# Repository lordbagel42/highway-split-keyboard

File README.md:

# Turing Split - HIGHWAY

<sub>this ^ will be replaced with a photo of the actual keyboard once it's built</sub>

## why?

I type a lot. Like, an insane amount. I write code for my robotics team and a lot for Hack Club, so I need a decent keyboard.
I've been using the Apple Magic Keyboard for a long while, and it's honestly quite nice. I originally bought it because my Quest 2 can track it.

However, I also am prone to carpal tunnel and other hand/fingie-issues, so I figured I should get a keyboard.
This led me to a discovery: Keyboards, are not cheap.

Then I discovered Highway and had a thought: make someone else pay for my keyboard.

## my keyboard design

I was tempted to go all out and build a full desk size keyboard contraption, but then I found [ergogen](https://ergogen.ceoloide.com/?exp=kicanvas) and decided to make an ergonomic, split-deck keyboard.
I based this off of a lot of random keyboards I saw throughout the internet and had one main focus when designing: comfortable, but not confusing.

I like layers. I plan to use them. I also want to have enough buttons I can do things easily and without thinking. If I wanted chords, I would have made a stenography keyboard.

This isn't the most complicated design, it's not the most simple, but it is mine, and I feel happy with it.

## the bom

Overall, the cost comes out to about $180 w/ tax.

| ITEM                  | SUPPLIER        | COUNT | UNIT COST | ROW COST | LOW BUDGET USE | HIGH BUDGET USE |
| --------------------- | --------------- | ----- | --------- | -------- | -------------- | --------------- |
| nice!nano v2          | typeractive.xyz | 1     | $25.00    | $25.00   | 17%            | 7%              |
| nice!view             | typeractive.xyz | 1     | $20.00    | $20.00   | 13%            | 6%              |
| PCB                   | JLCPCB          | 1     | $12.00    | $12.00   | 8%             | 3%              |
| PCB Shipping          | JLCPCB          | 1     | $25.00    | $25.00   | 17%            | 7%              |
| Kailh Hotswap Sockets | typeractive.xyz | 60    | $0.15     | $9.00    | 6%             | 3%              |
| Battery Jack          | typeractive.xyz | 2     | $0.50     | $1.00    | 1%             | 0%              |
| 1.5u Keycap           | typeractive.xyz | 4     | $0.50     | $2.00    | 1%             | 1%              |
| Homing Keycap         | typeractive.xyz | 2     | $0.50     | $1.00    | 1%             | 0%              |
| Keycap                | typeractive.xyz | 50    | $0.40     | $20.00   | 13%            | 6%              |
| Choc Switches         | typeractive.xyz | 60    | $0.55     | $33.00   | 22%            | 9%              |
| Diodes                | typeractive.xyz | 60    | $0.08     | $4.50    | 3%             | 1%              |
| Power Switch          | typeractive.xyz | 2     | $0.75     | $1.50    | 1%             | 0%              |
| Sockets and Pins      | typeractive.xyz | 2     | $6.50     | $13.00   | 9%             | 4%              |
| Encoder               | aliexpress      | 2     | $1.10     | $2.20    | 1%             | 1%              |

## notes

Something to note about this is a bit of a habit I've picked up from my apple keyboard: I don't like thick keyboards. My magic keyboard is maybe 7 millimeters tall at maximum and about 3 at the minimum. I am okay with something a bit thicker, but I don't want something as thick as a normal keyboard.

This is also part of why I went for low profile keys and keycaps, hence the Choc switches instead of the more common MX switches.

I also don't want a case to help with that. Because of the requirements for Highway, I have one. It's a very thin case designed to be lasercut using acrylic and 3d printed standoffs.

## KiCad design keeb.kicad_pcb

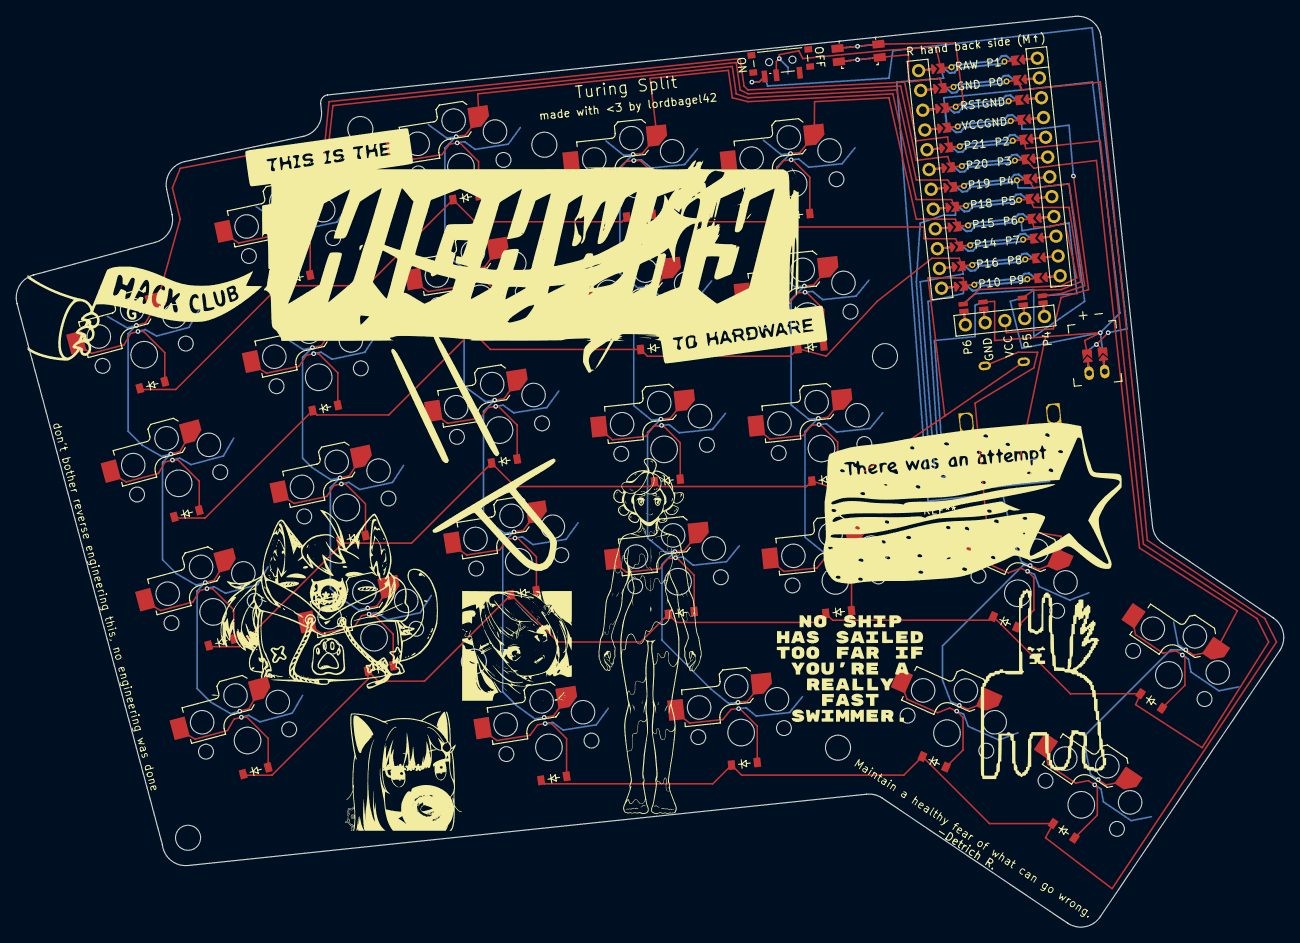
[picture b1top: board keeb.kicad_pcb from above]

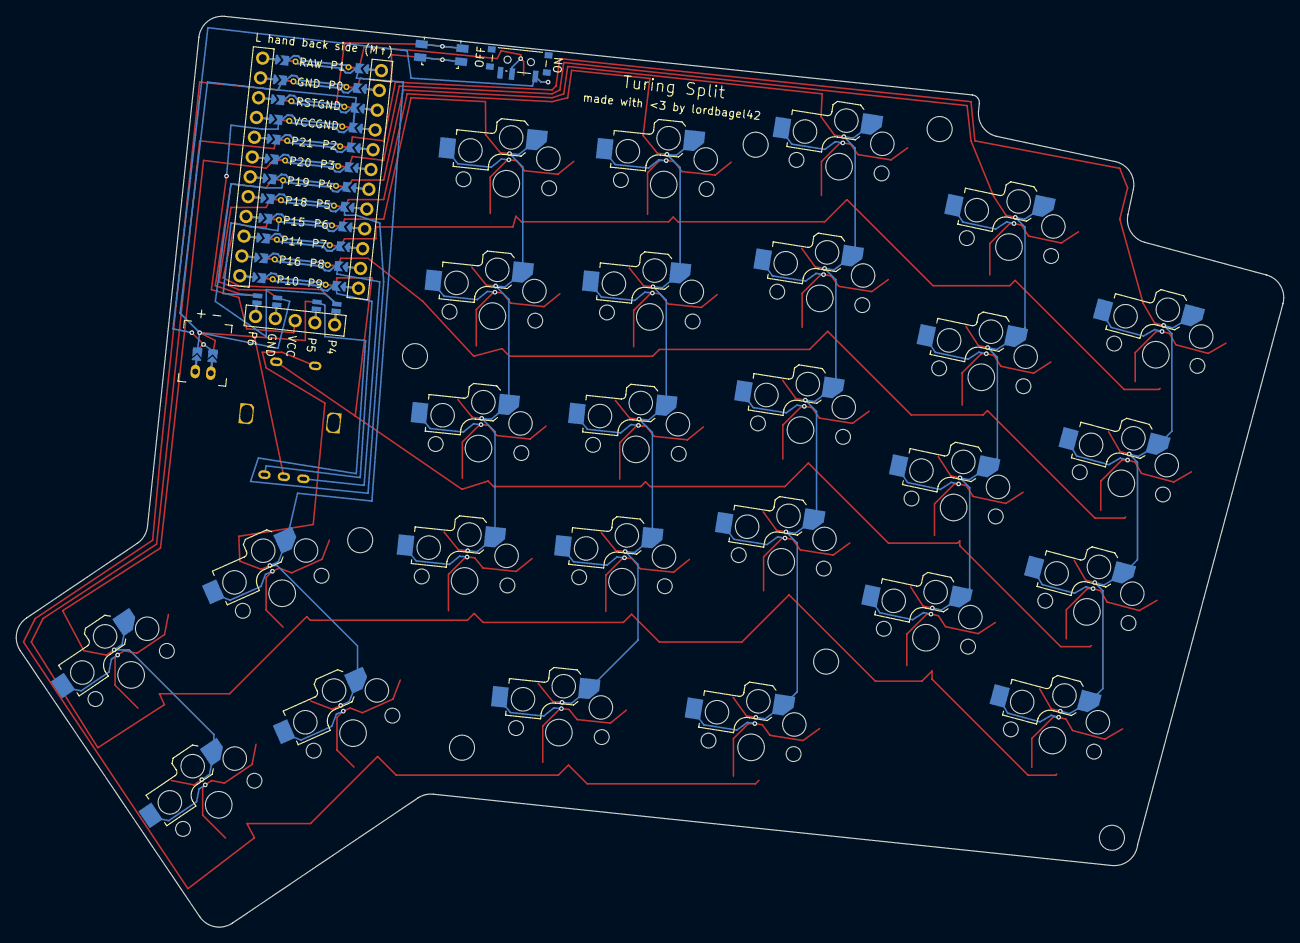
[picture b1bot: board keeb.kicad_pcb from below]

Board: 2 copper layers, 161.9 x 116.3 mm, 60 parts (27 on the bottom side), 54 nets.

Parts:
D1, D2, D3, D4, D5, D6, D7, D8, D9, D10, D11, D12, D13, D14, D15, D16, D17, D18, D19, D20, D21, D22, D23, D24, D25, D26: diode_tht_sod123
DISP1: display_nice_view
JST1: battery_connector_jst_ph_2
MCU1: mcu_nice_nano
Maintain a healthy fear of what can go wrong.: -Detrich R.; maintainfear
PWR1: power_switch_smd_side
RE1: rotary_encoder_ec11_ec12
RST1: reset_switch_smd_side
S1, S2, S3, S4, S5, S6, S7, S8, S9, S10, S11, S12, S13, S14, S15, S16, S17, S18, S19, S20, S21, S22, S23, S24, S25, S26: switch_choc_v1_v2
don't bother reverse engineering this, no engineering was done: Untitled

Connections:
BAT_P: JST1.1, PWR1.1, PWR1.3
DISP1_1: DISP1.1, DISP1.10, DISP1.23
DISP1_2: DISP1.2, DISP1.11, DISP1.22
DISP1_4: DISP1.4, DISP1.12, DISP1.21
DISP1_5: DISP1.5, DISP1.13, DISP1.20
GND: DISP1.15, DISP1.25, JST1.2, MCU1.103, MCU1.104, MCU1.123, RE1.B, RST1.2, RST1.4
JST1_1: JST1.11, JST1.21, JST1.31
JST1_2: JST1.12, JST1.22, JST1.32
P0: D13.1, D22.1, D24.1, D26.1, MCU1.102
P1: MCU1.101, RE1.S1, S23.1, S24.1
P2: D1.1, D5.1, D9.1, D14.1, D18.1, D23.1, D25.1, MCU1.105
P3: MCU1.106, S25.1, S26.1
P4: DISP1.17, DISP1.27, MCU1.107
P5: DISP1.16, DISP1.26, MCU1.108
P6: DISP1.14, DISP1.24, MCU1.109
P8: MCU1.111, RE1.C
P9: MCU1.112, RE1.A
P10: D2.1, D6.1, D10.1, D15.1, D19.1, MCU1.113, RE1.S2
P14: D4.1, D8.1, D12.1, D17.1, D21.1, MCU1.115
P15: MCU1.116, S18.1, S19.1, S20.1, S21.1
P16: D3.1, D7.1, D11.1, D16.1, D20.1, MCU1.114
P18: MCU1.117, S14.1, S15.1, S16.1, S17.1, S22.1
P19: MCU1.118, S9.1, S10.1, S11.1, S12.1, S13.1
P20: MCU1.119, S5.1, S6.1, S7.1, S8.1
P21: MCU1.120, S1.1, S2.1, S3.1, S4.1
RAW: MCU1.124, PWR1.2
RST: MCU1.122, RST1.1, RST1.3
VCC: DISP1.3, MCU1.121
first_bottom: D24.2, S24.2
first_top: D23.2, S23.2
index_bottom: D14.2, S14.2
index_home: D15.2, S15.2
index_number: D17.2, S17.2
index_top: D16.2, S16.2
inner_bottom: D18.2, S18.2
inner_home: D19.2, S19.2
inner_number: D21.2, S21.2
inner_top: D20.2, S20.2
middle_additional: D13.2, S13.2
middle_bottom: D9.2, S9.2
middle_home: D10.2, S10.2
middle_number: D12.2, S12.2
middle_top: D11.2, S11.2
pinky_bottom: D1.2, S1.2
pinky_home: D2.2, S2.2
pinky_number: D4.2, S4.2
pinky_top: D3.2, S3.2
ring_bottom: D5.2, S5.2
ring_home: D6.2, S6.2
ring_number: D8.2, S8.2
ring_top: D7.2, S7.2
second_bottom: D26.2, S26.2
second_top: D25.2, S25.2
space_top: D22.2, S22.2

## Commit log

2025-05-25 6:46am 2025-05-25
2025-05-27 add the keyboard
2025-05-27 finished!
2025-05-29 remove exccess gerber files
2025-05-29 add BOM
2025-05-29 add mounting holes
2025-05-29 ship!
